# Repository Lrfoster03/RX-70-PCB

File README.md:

# RX-70-PCB
KiCAD files for RX-70 PCB

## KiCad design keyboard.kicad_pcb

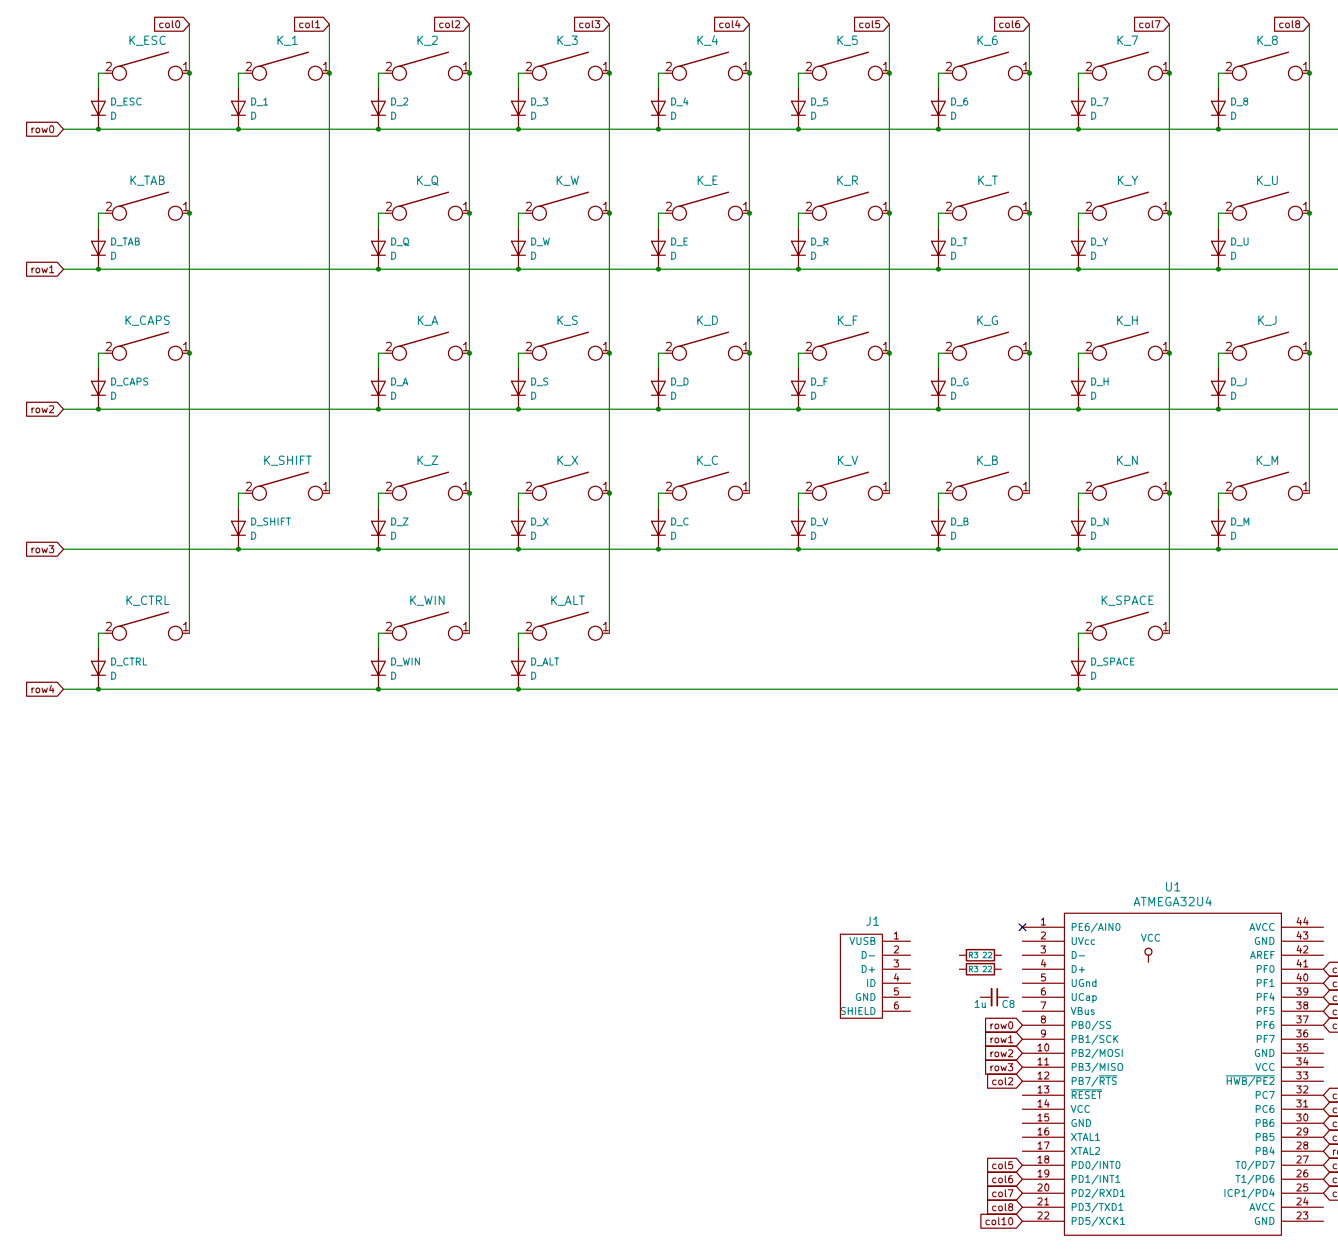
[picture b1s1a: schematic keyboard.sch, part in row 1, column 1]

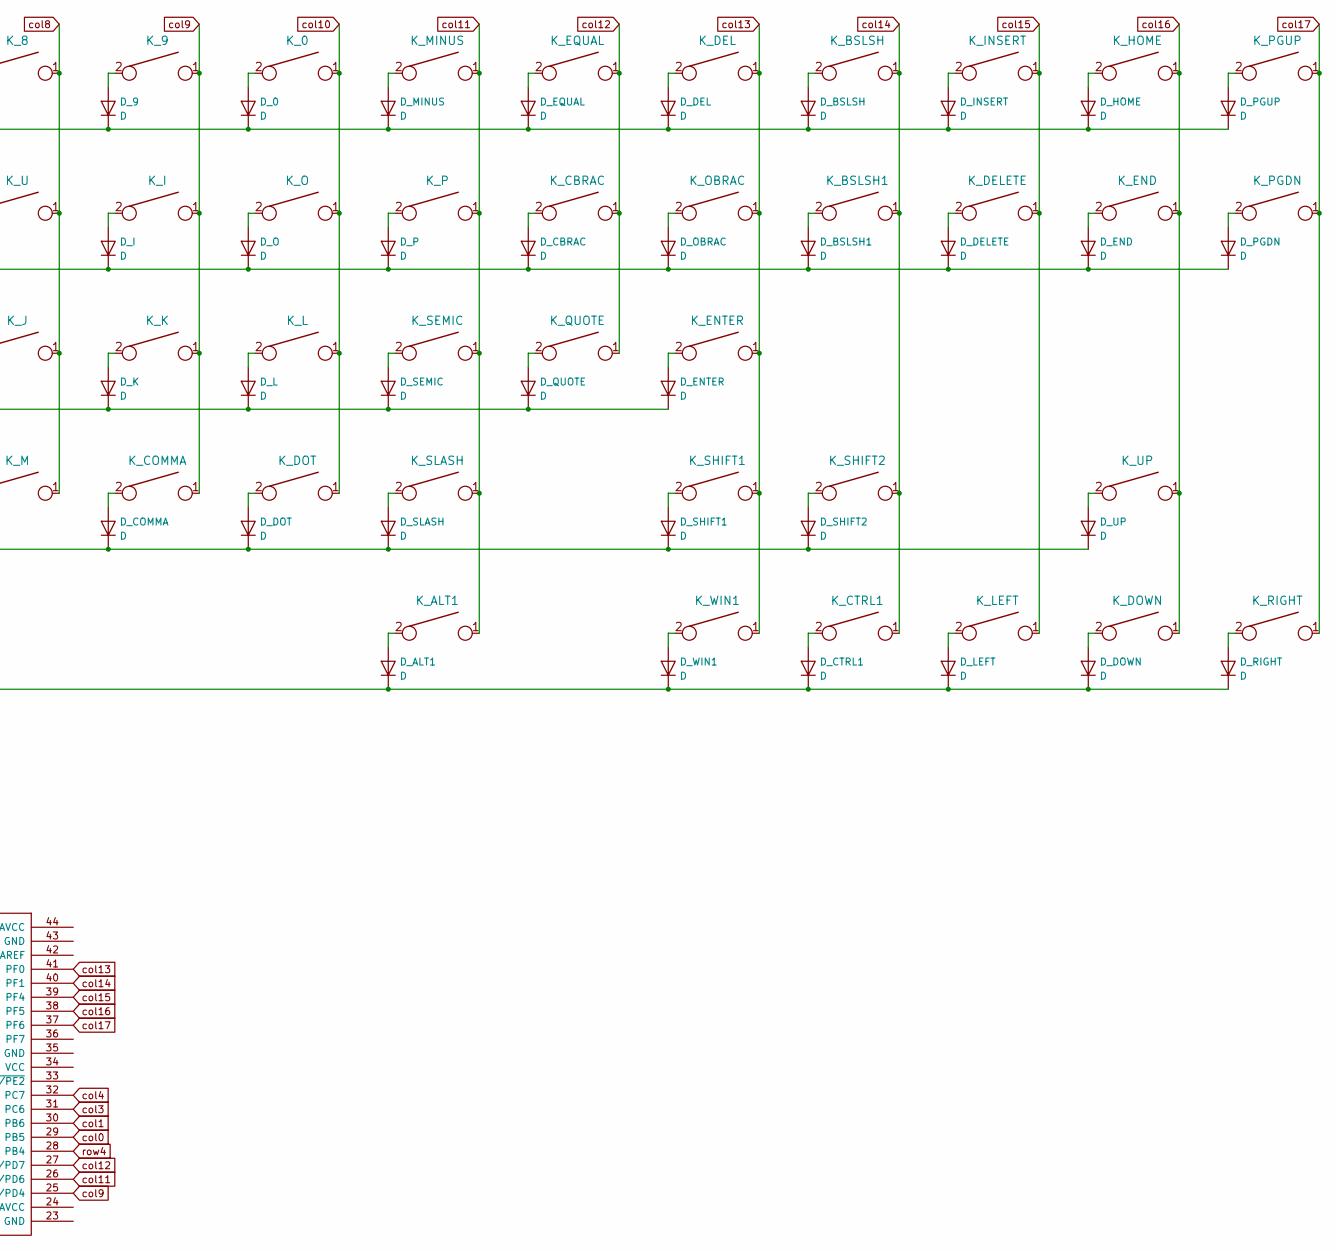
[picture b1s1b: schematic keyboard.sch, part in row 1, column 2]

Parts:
C8: 1u; C_0805_2012Metric_Pad1.15x1.40mm_HandSolder
D_0, D_1, D_2, D_3, D_4, D_5, D_6, D_7, D_8, D_9: D; D_SOD123_axial
D_A: D; D_SOD123_axial
D_ALT, D_ALT1: D; D_SOD123_axial
D_B: D; D_SOD123_axial
D_BSLSH, D_BSLSH1: D; D_SOD123_axial
D_C: D; D_SOD123_axial
D_CAPS: D; D_SOD123_axial
D_CBRAC: D; D_SOD123_axial
D_COMMA: D; D_SOD123_axial
D_CTRL, D_CTRL1: D; D_SOD123_axial
D_D: D; D_SOD123_axial
D_DEL: D; D_SOD123_axial
D_DELETE: D; D_SOD123_axial
D_DOT: D; D_SOD123_axial
D_DOWN: D; D_SOD123_axial
D_E: D; D_SOD123_axial
D_END: D; D_SOD123_axial
D_ENTER: D; D_SOD123_axial
D_EQUAL: D; D_SOD123_axial
D_ESC: D; D_SOD123_axial
D_F: D; D_SOD123_axial
D_G: D; D_SOD123_axial
D_H: D; D_SOD123_axial
D_HOME: D; D_SOD123_axial
D_I: D; D_SOD123_axial
D_INSERT: D; D_SOD123_axial
D_J: D; D_SOD123_axial
D_K: D; D_SOD123_axial
D_L: D; D_SOD123_axial
D_LEFT: D; D_SOD123_axial
D_M: D; D_SOD123_axial
D_MINUS: D; D_SOD123_axial
D_N: D; D_SOD123_axial
D_O: D; D_SOD123_axial
D_OBRAC: D; D_SOD123_axial
D_P: D; D_SOD123_axial
D_PGDN: D; D_SOD123_axial
D_PGUP: D; D_SOD123_axial
D_Q: D; D_SOD123_axial
D_QUOTE: D; D_SOD123_axial
D_R: D; D_SOD123_axial
D_RIGHT: D; D_SOD123_axial
D_S: D; D_SOD123_axial
D_SEMIC: D; D_SOD123_axial
D_SHIFT, D_SHIFT1, D_SHIFT2: D; D_SOD123_axial
D_SLASH: D; D_SOD123_axial
D_SPACE: D; D_SOD123_axial
D_T: D; D_SOD123_axial
D_TAB: D; D_SOD123_axial
D_U: D; D_SOD123_axial
D_UP: D; D_SOD123_axial
D_V: D; D_SOD123_axial
D_W: D; D_SOD123_axial
D_WIN, D_WIN1: D; D_SOD123_axial
D_X: D; D_SOD123_axial
D_Y: D; D_SOD123_axial
D_Z: D; D_SOD123_axial
J1: USB_mini_micro_B; USB_miniB_hirose_5S8
K_0, K_1, K_2, K_3, K_4, K_5, K_6, K_7, K_8, K_9: KEYSW; MX-1U-NoLED
K_A: KEYSW; MX-1U-NoLED
K_ALT, K_ALT1: KEYSW; MX-1.5U-NoLED
K_B: KEYSW; MX-1U-NoLED
K_BSLSH: KEYSW; MX-1U-NoLED
K_BSLSH1: KEYSW; MX-1.5U-NoLED
K_C: KEYSW; MX-1U-NoLED
K_CAPS: KEYSW; MX-1.75U-NoLED
K_CBRAC: KEYSW; MX-1U-NoLED
K_COMMA: KEYSW; MX-1U-NoLED
K_CTRL, K_CTRL1: KEYSW; MX-1.5U-NoLED
K_D: KEYSW; MX-1U-NoLED
K_DEL: KEYSW; MX-1U-NoLED
K_DELETE: KEYSW; MX-1U-NoLED
K_DOT: KEYSW; MX-1U-NoLED
K_DOWN: KEYSW; MX-1U-NoLED
K_E: KEYSW; MX-1U-NoLED
K_END: KEYSW; MX-1U-NoLED
K_ENTER: KEYSW; MX-2.25U-NoLED
K_EQUAL: KEYSW; MX-1U-NoLED
K_ESC: KEYSW; MX-1U-NoLED
K_F: KEYSW; MX-1U-NoLED
K_G: KEYSW; MX-1U-NoLED
K_H: KEYSW; MX-1U-NoLED
K_HOME: KEYSW; MX-1U-NoLED
K_I: KEYSW; MX-1U-NoLED
K_INSERT: KEYSW; MX-1U-NoLED
K_J: KEYSW; MX-1U-NoLED
K_K: KEYSW; MX-1U-NoLED
K_L: KEYSW; MX-1U-NoLED
K_LEFT: KEYSW; MX-1U-NoLED
K_M: KEYSW; MX-1U-NoLED
K_MINUS: KEYSW; MX-1U-NoLED
K_N: KEYSW; MX-1U-NoLED
K_O: KEYSW; MX-1U-NoLED
K_OBRAC: KEYSW; MX-1U-NoLED
K_P: KEYSW; MX-1U-NoLED
K_PGDN: KEYSW; MX-1U-NoLED
K_PGUP: KEYSW; MX-1U-NoLED
K_Q: KEYSW; MX-1U-NoLED
K_QUOTE: KEYSW; MX-1U-NoLED
K_R: KEYSW; MX-1U-NoLED
K_RIGHT: KEYSW; MX-1U-NoLED
K_S: KEYSW; MX-1U-NoLED
K_SEMIC: KEYSW; MX-1U-NoLED
K_SHIFT: KEYSW; MX-2.25U-NoLED
K_SHIFT1: KEYSW; MX-1.75U-NoLED
K_SHIFT2: KEYSW; MX-1U-NoLED
K_SLASH: KEYSW; MX-1U-NoLED
K_SPACE: KEYSW; MX-7U-NoLED
K_T: KEYSW; MX-1U-NoLED
K_TAB: KEYSW; MX-1.5U-NoLED
K_U: KEYSW; MX-1U-NoLED
K_UP: KEYSW; MX-1U-NoLED
K_V: KEYSW; MX-1U-NoLED
K_W: KEYSW; MX-1U-NoLED
K_WIN, K_WIN1: KEYSW; MX-1U-NoLED
K_X: KEYSW; MX-1U-NoLED
K_Y: KEYSW; MX-1U-NoLED
K_Z: KEYSW; MX-1U-NoLED
R3: 22; R_0805_2012Metric_Pad1.15x1.40mm_HandSolder
U1: ATMEGA32U4; TQFP-44_10x10mm_P0.8mm

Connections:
/col0: K_CAPS.1, K_CTRL.1, K_ESC.1, K_TAB.1, U1.29 (PB5); also elsewhere on the board
/col1: K_1.1, K_SHIFT.1, U1.30 (PB6); also elsewhere on the board
/col2: K_2.1, K_A.1, K_Q.1, K_WIN.1, K_Z.1, U1.12 (PB7/~RTS); also elsewhere on the board
/col3: K_3.1, K_ALT.1, K_S.1, K_W.1, K_X.1, U1.31 (PC6); also elsewhere on the board
/col4: K_4.1, K_C.1, K_D.1, K_E.1, U1.32 (PC7); also elsewhere on the board
/col5: K_5.1, K_F.1, K_R.1, K_V.1, U1.18 (PD0/INT0); also elsewhere on the board
/col6: K_6.1, K_B.1, K_G.1, K_T.1, U1.19 (PD1/INT1); also elsewhere on the board
/col7: K_7.1, K_H.1, K_N.1, K_SPACE.1, K_Y.1, U1.20 (PD2/RXD1); also elsewhere on the board
/col8: K_8.1, K_J.1, K_M.1, K_U.1, U1.21 (PD3/TXD1); also elsewhere on the board
/col9: K_9.1, K_COMMA.1, K_I.1, K_K.1, U1.25 (ICP1/PD4); also elsewhere on the board
/col10: K_0.1, K_DOT.1, K_L.1, K_O.1, U1.22 (PD5/XCK1); also elsewhere on the board
/col11: K_ALT1.1, K_MINUS.1, K_P.1, K_SEMIC.1, K_SLASH.1, U1.26 (T1/PD6); also elsewhere on the board
/col12: K_CBRAC.1, K_EQUAL.1, K_QUOTE.1, U1.27 (T0/PD7); also elsewhere on the board
/col13: K_DEL.1, K_ENTER.1, K_OBRAC.1, K_SHIFT1.1, K_WIN1.1, U1.41 (PF0); also elsewhere on the board
/col14: K_BSLSH.1, K_BSLSH1.1, K_CTRL1.1, K_SHIFT2.1, U1.40 (PF1); also elsewhere on the board
/col15: K_DELETE.1, K_INSERT.1, K_LEFT.1, U1.39 (PF4); also elsewhere on the board
/col16: K_DOWN.1, K_END.1, K_HOME.1, K_UP.1, U1.38 (PF5); also elsewhere on the board
/col17: K_PGDN.1, K_PGUP.1, K_RIGHT.1, U1.37 (PF6); also elsewhere on the board
/row0: D_0.1 (K), D_1.1 (K), D_2.1 (K), D_3.1 (K), D_4.1 (K), D_5.1 (K), D_6.1 (K), D_7.1 (K), D_8.1 (K), D_9.1 (K), D_BSLSH.1 (K), D_DEL.1 (K), D_EQUAL.1 (K), D_ESC.1 (K), D_HOME.1 (K), D_INSERT.1 (K), D_MINUS.1 (K), D_PGUP.1 (K), U1.8 (PB0/SS); also elsewhere on the board
/row1: D_BSLSH1.1 (K), D_CBRAC.1 (K), D_DELETE.1 (K), D_E.1 (K), D_END.1 (K), D_I.1 (K), D_O.1 (K), D_OBRAC.1 (K), D_P.1 (K), D_PGDN.1 (K), D_Q.1 (K), D_R.1 (K), D_T.1 (K), D_TAB.1 (K), D_U.1 (K), D_W.1 (K), D_Y.1 (K), U1.9 (PB1/SCK); also elsewhere on the board
/row2: D_A.1 (K), D_CAPS.1 (K), D_D.1 (K), D_ENTER.1 (K), D_F.1 (K), D_G.1 (K), D_H.1 (K), D_J.1 (K), D_K.1 (K), D_L.1 (K), D_QUOTE.1 (K), D_S.1 (K), D_SEMIC.1 (K), U1.10 (PB2/MOSI); also elsewhere on the board
/row3: D_B.1 (K), D_C.1 (K), D_COMMA.1 (K), D_DOT.1 (K), D_M.1 (K), D_N.1 (K), D_SHIFT.1 (K), D_SHIFT1.1 (K), D_SHIFT2.1 (K), D_SLASH.1 (K), D_UP.1 (K), D_V.1 (K), D_X.1 (K), D_Z.1 (K), U1.11 (PB3/MISO); also elsewhere on the board
/row4: D_ALT.1 (K), D_ALT1.1 (K), D_CTRL.1 (K), D_CTRL1.1 (K), D_DOWN.1 (K), D_LEFT.1 (K), D_RIGHT.1 (K), D_SPACE.1 (K), D_WIN.1 (K), D_WIN1.1 (K), U1.28 (PB4); also elsewhere on the board
GND: C8.2; also elsewhere on the board
unnamed 24: C8.1; also elsewhere on the board
unnamed: D_0.2 (A), K_0.2
unnamed: D_1.2 (A), K_1.2
unnamed: D_2.2 (A), K_2.2
unnamed: D_3.2 (A), K_3.2
unnamed: D_4.2 (A), K_4.2
unnamed: D_5.2 (A), K_5.2
unnamed: D_6.2 (A), K_6.2
unnamed: D_7.2 (A), K_7.2
unnamed: D_8.2 (A), K_8.2
unnamed: D_9.2 (A), K_9.2
unnamed: D_A.2 (A), K_A.2
unnamed: D_ALT1.2 (A), K_ALT1.2
unnamed: D_ALT.2 (A), K_ALT.2
unnamed: D_B.2 (A), K_B.2
unnamed: D_BSLSH1.2 (A), K_BSLSH1.2
unnamed: D_BSLSH.2 (A), K_BSLSH.2
unnamed: D_C.2 (A), K_C.2
unnamed: D_CAPS.2 (A), K_CAPS.2
unnamed: D_CBRAC.2 (A), K_CBRAC.2
unnamed: D_COMMA.2 (A), K_COMMA.2
unnamed: D_CTRL1.2 (A), K_CTRL1.2
unnamed: D_CTRL.2 (A), K_CTRL.2
unnamed: D_D.2 (A), K_D.2
unnamed: D_DEL.2 (A), K_DEL.2
unnamed: D_DELETE.2 (A), K_DELETE.2
unnamed: D_DOT.2 (A), K_DOT.2
unnamed: D_DOWN.2 (A), K_DOWN.2
unnamed: D_E.2 (A), K_E.2
unnamed: D_END.2 (A), K_END.2
unnamed: D_ENTER.2 (A), K_ENTER.2
unnamed: D_EQUAL.2 (A), K_EQUAL.2
unnamed: D_ESC.2 (A), K_ESC.2
unnamed: D_F.2 (A), K_F.2
unnamed: D_G.2 (A), K_G.2
unnamed: D_H.2 (A), K_H.2
unnamed: D_HOME.2 (A), K_HOME.2
unnamed: D_I.2 (A), K_I.2
unnamed: D_INSERT.2 (A), K_INSERT.2
unnamed: D_J.2 (A), K_J.2
unnamed: D_K.2 (A), K_K.2
unnamed: D_L.2 (A), K_L.2
unnamed: D_LEFT.2 (A), K_LEFT.2
unnamed: D_M.2 (A), K_M.2
unnamed: D_MINUS.2 (A), K_MINUS.2
unnamed: D_N.2 (A), K_N.2
unnamed: D_O.2 (A), K_O.2
unnamed: D_OBRAC.2 (A), K_OBRAC.2
unnamed: D_P.2 (A), K_P.2
unnamed: D_PGDN.2 (A), K_PGDN.2
unnamed: D_PGUP.2 (A), K_PGUP.2
unnamed: D_Q.2 (A), K_Q.2
unnamed: D_QUOTE.2 (A), K_QUOTE.2
unnamed: D_R.2 (A), K_R.2
unnamed: D_RIGHT.2 (A), K_RIGHT.2
unnamed: D_S.2 (A), K_S.2
unnamed: D_SEMIC.2 (A), K_SEMIC.2
unnamed: D_SHIFT1.2 (A), K_SHIFT1.2
unnamed: D_SHIFT2.2 (A), K_SHIFT2.2
unnamed: D_SHIFT.2 (A), K_SHIFT.2
unnamed: D_SLASH.2 (A), K_SLASH.2
unnamed: D_SPACE.2 (A), K_SPACE.2
unnamed: D_T.2 (A), K_T.2
unnamed: D_TAB.2 (A), K_TAB.2
unnamed: D_U.2 (A), K_U.2
unnamed: D_UP.2 (A), K_UP.2
unnamed: D_V.2 (A), K_V.2
unnamed: D_W.2 (A), K_W.2
unnamed: D_WIN1.2 (A), K_WIN1.2
unnamed: D_WIN.2 (A), K_WIN.2
unnamed: D_X.2 (A), K_X.2
unnamed: D_Y.2 (A), K_Y.2
unnamed: D_Z.2 (A), K_Z.2

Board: 2 copper layers, 159 parts (15 on the bottom side), 106 nets, no tracks yet.

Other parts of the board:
C9, C10, C11, C12, C13, C14: 22pF; C_0805_2012Metric_Pad1.15x1.40mm_HandSolder
R5, R6: 10k; R_0805_2012Metric_Pad1.15x1.40mm_HandSolder
R7, R8: 22; R_0805_2012Metric_Pad1.15x1.40mm_HandSolder
SW1: SW_PUSH; SW_SPST_TL3342
U2: ATMEGA32U4; TQFP-44_10x10mm_P0.8mm
USB2: Molex-0548190589; Molex-0548190589-Assembly
X2: XTAL_GND; Crystal_SMD_5032-4Pin_5.0x3.2mm

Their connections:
/col0: U2.29; also elsewhere on the board
/col1: U2.30; also elsewhere on the board
/col2: U2.12; also elsewhere on the board
/col3: U2.31; also elsewhere on the board
/col4: U2.32; also elsewhere on the board
/col5: U2.18; also elsewhere on the board
/col6: U2.19; also elsewhere on the board
/col7: U2.20; also elsewhere on the board
/col8: U2.21; also elsewhere on the board
/col9: U2.25; also elsewhere on the board
/col10: U2.22; also elsewhere on the board
/col11: U2.26; also elsewhere on the board
/col12: U2.27; also elsewhere on the board
/col13: U2.41; also elsewhere on the board
/col14: U2.40; also elsewhere on the board
/col15: U2.39; also elsewhere on the board
/col16: U2.38; also elsewhere on the board
/col17: U2.37; also elsewhere on the board
/row0: U2.8; also elsewhere on the board
/row1: U2.9; also elsewhere on the board
/row2: U2.10; also elsewhere on the board
/row3: U2.11; also elsewhere on the board
/row4: U2.28; also elsewhere on the board
GND: C9.2, C10.2, C11.2, C12.2, C13.2, C14.2, R6.2, SW1.1, U2.5, U2.15, U2.23, USB2.1, X2.2, X2.4; also elsewhere on the board
unnamed 24: U2.16, X2.1; also elsewhere on the board
unnamed: C9.1, U2.17, X2.3
unnamed: C10.1, U2.6
unnamed: R5.1, SW1.2, U2.13
unnamed: R6.1, U2.33
unnamed: R7.1, U2.3
unnamed: R8.1, U2.4
unnamed: R7.2, USB2.2
unnamed: R8.2, USB2.3
VCC: C11.1, C12.1, C13.1, C14.1, R5.2, U2.2, U2.14, U2.24, USB2.5

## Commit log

2024-02-08 Began PCB design
2024-02-08 Testing
